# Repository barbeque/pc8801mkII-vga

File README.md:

# PC-8801mkII VGA
This is a video adapter I built to go from my 1984 NEC PC-8801mkII's 3-bit digital RGB-out port to a VGA monitor. If you have an SR or newer, you can (and should) just use analogue RGB to VGA adapters instead.

Please note that this is just a level shifter and pinout adapter. It is _not_ a scan converter; if your monitor is not capable of 15kHz (or 24kHz for some machines) video, it will not work with this adapter. In other words, your monitor must match the output sync rate of the computer being adapted.

Please consult [the 15kHz modern monitors list](http://15khz.wikidot.com/) for models of monitor which may work with this adapter.

This board was developed as part of a project for [the Leaded Solder blog](https://www.leadedsolder.com/). Chances are, if you have a computer that needs this adapter, you will probably enjoy the other projects on the blog too. Please consider [backing the blog on Patreon](https://www.patreon.com/leadedsolder) to provide funds that will be used to make more open-source boards for the old-computer community.

# Current Status
**WORKING**, but improvements are likely to arrive in the coming days to deal with the "jailbar" interference pattern on some monitors.

# Version History
 - v1.8 (2025): In development.
 - v1.7 (2021): Added bypass capacitors that ruined the video quality. If you have one of these older boards (e.g. from PCBWay,) do not install the capacitors.

# Ordering a board
You can use files from the `gerber` directory, the zip files in the Releases section, or [order the board from the Shared Projects section of PCBway](https://www.pcbway.com/project/shareproject/NEC_PC_8801mkII_digital_RGB_video_to_VGA_adapter.html). Note that I receive a small PCBway credit for boards purchased through that platform.

# Bill of Materials
 * CUI SDS-80J 270-degree right-angle DIN female socket (CP-2380-ND)
 * TE AMP 1-1734530-1 VGA connector (A35116-ND)
 * 3x 150Ω through-hole resistors
 * 270° male-male 8-pin DIN cable (see below)
 
# Confirmed Working On
 * Fujitsu FM-7, Fujitsu FM-New7, Fujitsu FM-8
 * Hitachi Basic Master Level III Mark II
 * NEC PC-6001mkII (only 8 colour mode works, obviously)
 * NEC PC-8001, PC-8001mkIISR
 * NEC PC-8801mkII
 * NEC PC-9801UV
 * Sanyo MBC-550, MBC-555
 * Sony SMC-777 (8-colour mode)

# Display Devices Tested With
 * NEC MultiSync 1970NX LCD
 * NEC MultiSync 3D CRT
 * [GBS-Control upscaler](https://github.com/ramapcsx2/gbs-control)

# Assembly directions
 1. Solder both the VGA and DIN8 connectors to the board. The top side is the one marked with the LeadedSolder URL and the board name.
 2. Solder three 150Ω resistors into the spots for them in the middle of the board (Red, Green, Blue). The footprint is slightly too small for normal resistors, so I had to stand the resistor straight up and bend the other lead over.
 3. Connect the computer to the female DIN with a DIN8 extension cable such as the Ancable male-male 270° DIN8 cable (for Peavey Sanpera guitar pedals)
 4. Connect a 15/24kHz-capable VGA monitor (I use an NEC MultiSync 1970NX) to the female VGA connector with a standard VGA monitor cable.

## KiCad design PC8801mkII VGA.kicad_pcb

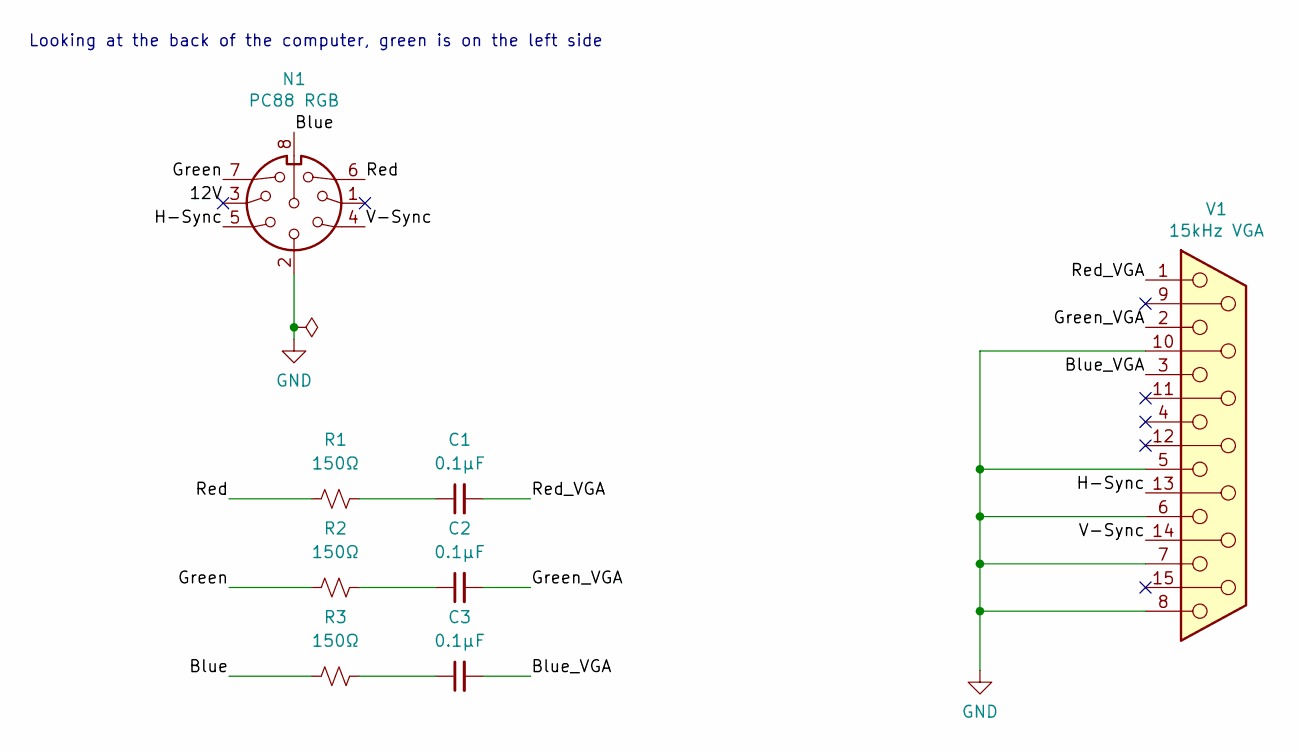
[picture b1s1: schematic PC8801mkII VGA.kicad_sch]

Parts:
C1, C2, C3: 0.1µF; C_Disc_D3.4mm_W2.1mm_P2.50mm
N1: PC88 RGB; CUI_SDS-80J
R1, R2, R3: 150Ω; R_Axial_DIN0207_L6.3mm_D2.5mm_P10.16mm_Horizontal
V1: 15kHz VGA; FIXED-1-1734530-1

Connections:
/12V: N1.3
/Blue: N1.8, R3.2
/Blue_VGA: C3.2, V1.3
/Green: N1.7, R2.2
/Green_VGA: C2.2, V1.2
/H-Sync: N1.5, V1.13
/Red: N1.6, R1.2
/Red_VGA: C1.2, V1.1
/V-Sync: N1.4, V1.14
GND: N1.2, N1.S1, N1.S2, V1.5, V1.6, V1.7, V1.8, V1.10, V1.16, V1.17
unnamed: C1.1, R1.1
unnamed: C2.1, R2.1
unnamed: C3.1, R3.1

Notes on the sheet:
Looking at the back of the computer, green is on the left side

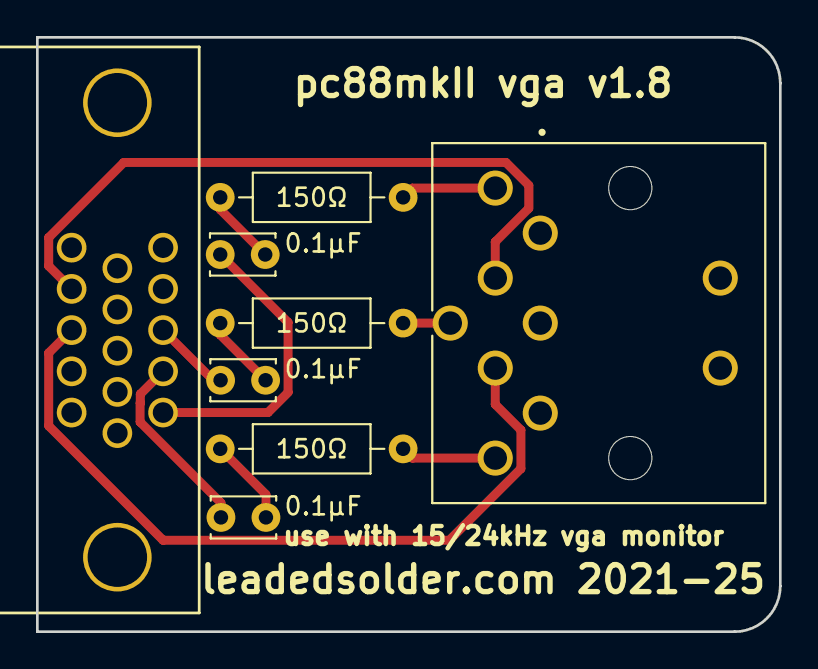
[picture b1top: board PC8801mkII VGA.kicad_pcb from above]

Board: 2 copper layers, 41.3 x 33.0 mm, 8 parts (0 on the bottom side), 12 nets.

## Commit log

2018-08-26 Really confusing board design that probably won't help me build this thing
2018-08-26 Use the 3-row right angle VGA connector which is all digikey seems to have
2018-08-26 Revision with ACTUAL PARTS
2018-08-26 Revised schematic based on the female pinout
2018-08-26 Add pointless silkscreen
2018-08-27 Ignore cache.lib
2018-09-11 Label resistors
2018-09-19 Revised footprint
2018-09-19 Flipped version using fixed footprint
2018-09-19 Now with easier-to-cut sync traces
2018-09-20 Flipped the connector so it actually lines up now
2018-09-24 V1.4 - the colour pins go to the right places now
2018-09-24 Auto-bodge
2018-09-24 Add warning label telling people the port is backwards from how it comes out of the PC88
2018-09-26 Try to route the green trace a little further away from the sync pins
2018-10-01 Bigger resistors, trying to shorten colour tracks, run sync far away from all colours
2018-10-14 Instructions
2018-12-02 Improve README
2018-12-02 Add DIN8 to BOM
2019-04-02 FM-7 update
2019-05-20 New7 confirmation
2019-11-16 README update
2019-11-22 Flipping 12V and Bonus aroundg
2019-11-22 Wait - the pin numbers were right in the first place
2019-11-23 Ground plane
2020-09-21 Fix the callout
2020-09-21 Move 12V to the right side
2020-09-21 Cleaning up
2021-03-23 Use decoupling caps
2021-12-05 Provide Gerbers
2021-12-05 Fixed readme, better gerbers
2022-12-18 Remove reference to decoupling caps, they're bad
2023-02-27 Hitachi confirmed functioning
2025-02-17 Prepare for new version
2025-02-17 KiCad 8; bring up to spec
2025-02-17 README rejig
2025-02-17 README status
2025-02-17 Revision again
2025-02-17 Version history
2025-02-17 v1.9 test release
2025-02-20 PCBway link

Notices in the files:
parts and their libraries:
Copyright 2016 Accelerated Designs. All rights reserved.
